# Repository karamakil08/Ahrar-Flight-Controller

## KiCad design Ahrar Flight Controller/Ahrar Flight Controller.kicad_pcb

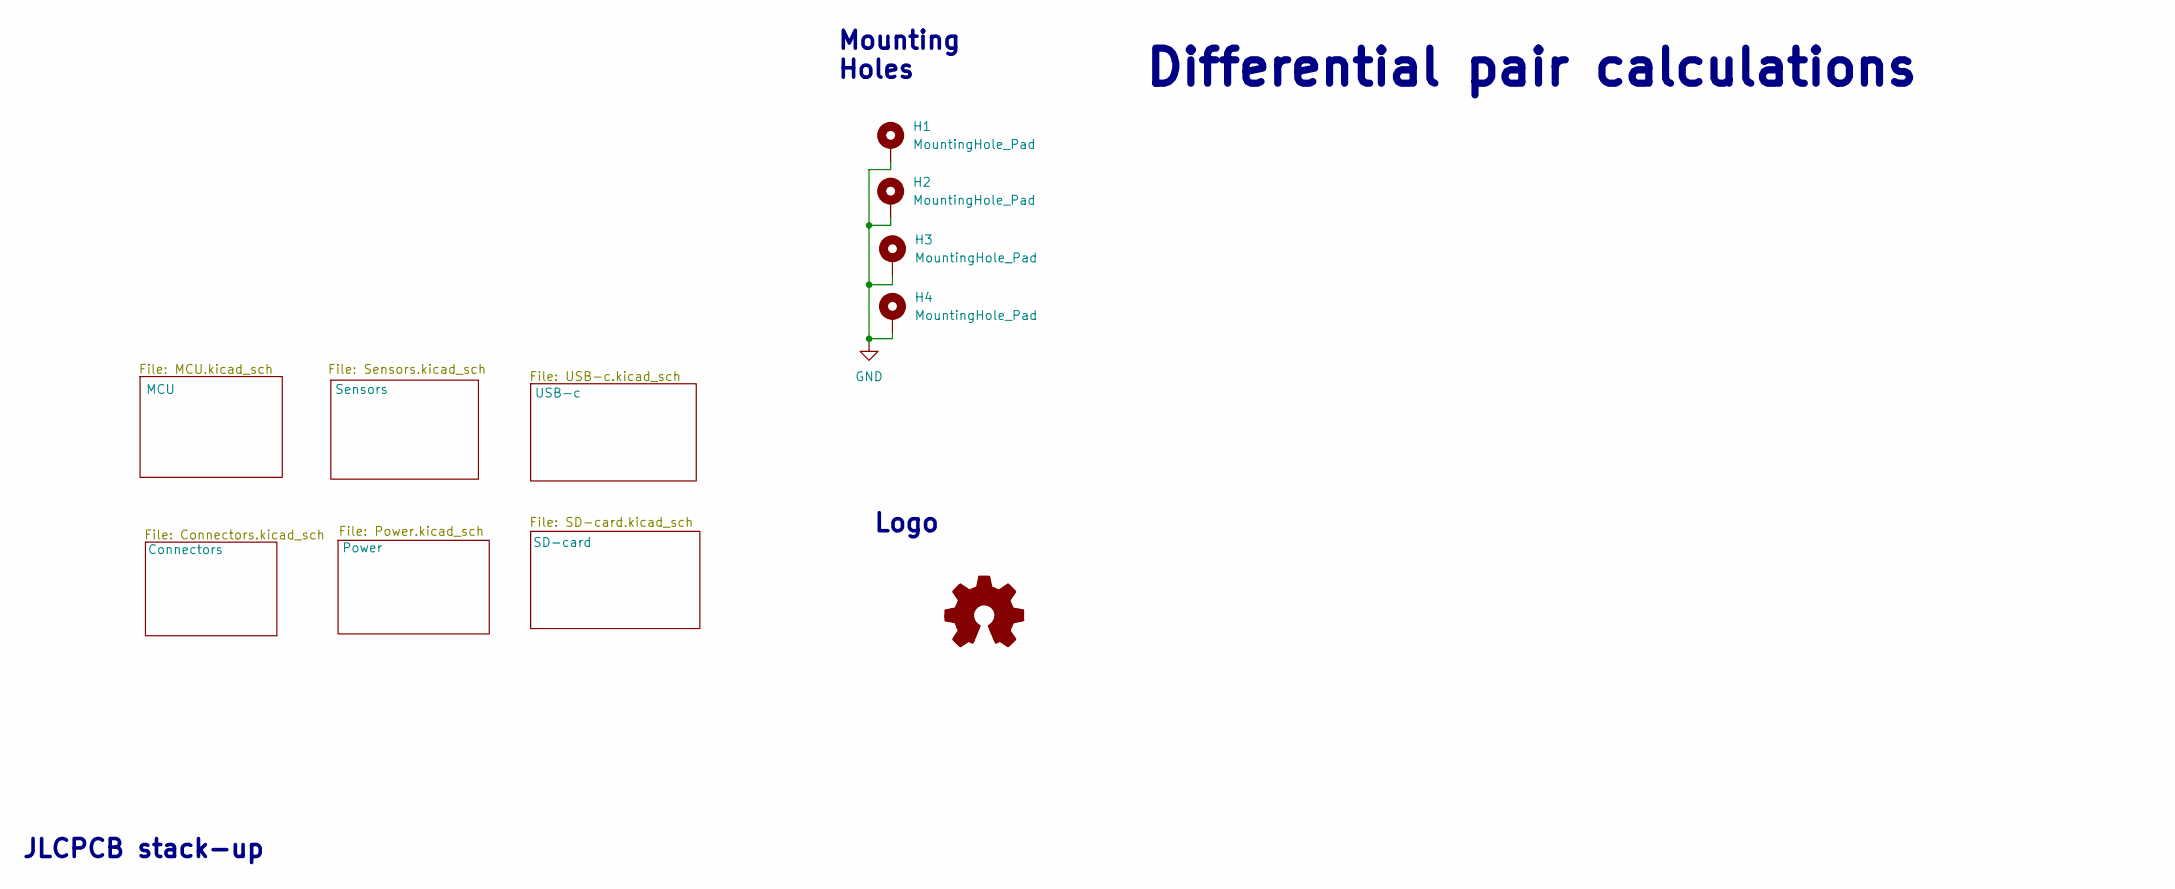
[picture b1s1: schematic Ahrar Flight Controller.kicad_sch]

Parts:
H1, H2, H3, H4: MountingHole_Pad; MountingHole_2.2mm_M2_Pad_Via
Logo1: Hananou logo

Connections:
GND: H1.1 (1_1), H2.1 (1_1), H3.1 (1_1), H4.1 (1_1); also elsewhere on the board

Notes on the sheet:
Differential pair calculations
Mounting Holes
JLCPCB stack-up
Logo

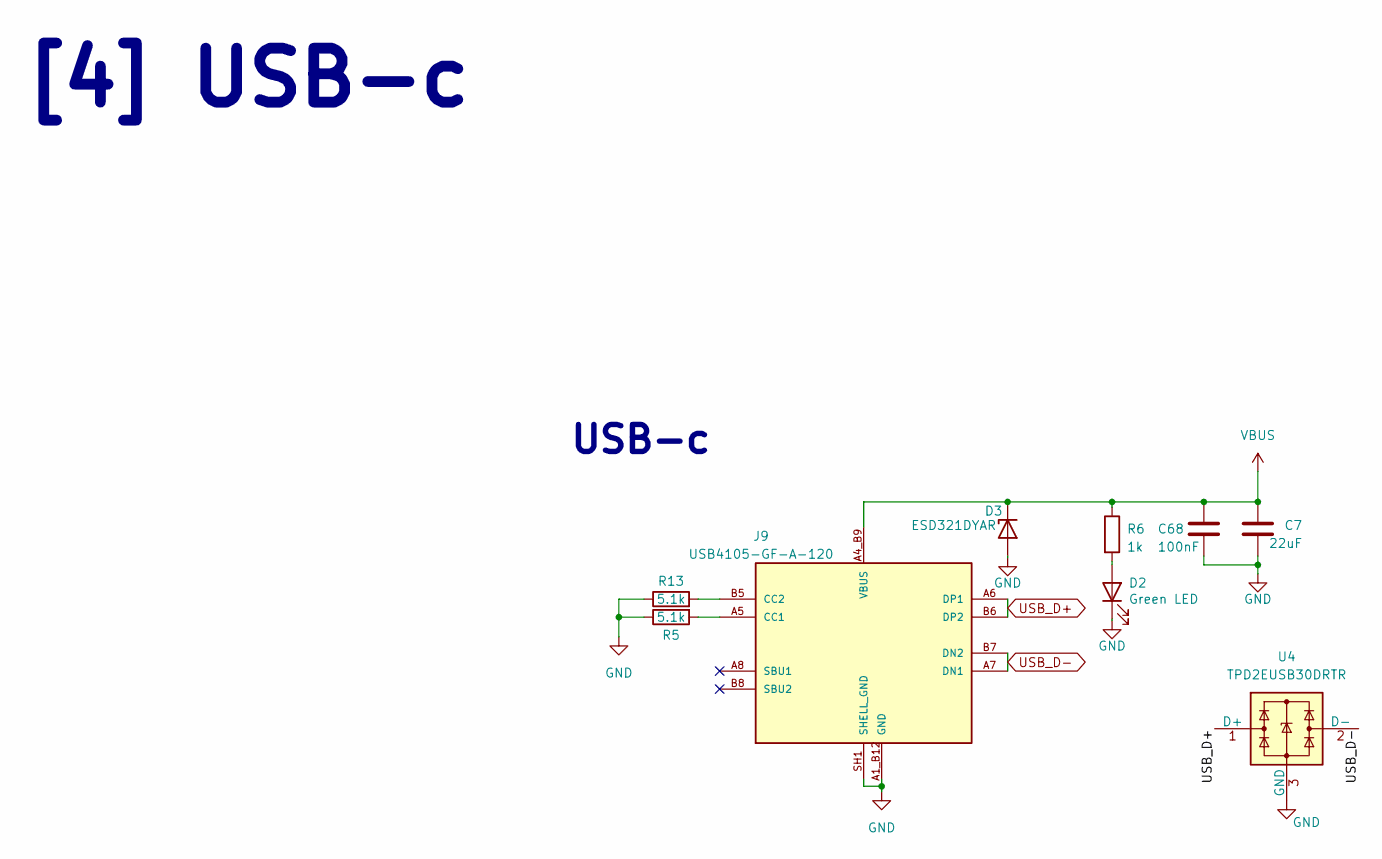
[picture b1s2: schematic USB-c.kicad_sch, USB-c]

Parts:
C7: 22uF; C_0805_2012Metric; Part Number CL21A226KOQNNNE
C68: 100nF; C_0402_1005Metric; Part Number GRM155R71C104KA88D
D2: Green LED; LED_0603_1608Metric; Part Number HL-PST-1608U51GC
D3: ESD321DYAR; D_SOD-523; Part Number ESD321DYAR
J9: USB4105-GF-A-120; GCT_USB4105-GF-A-120; Part Number USB4105-GF-A-120
R5, R13: 5.1k; R_0402_1005Metric; Part Number ERJ2RKF5101X
R6: 1k; R_0402_1005Metric; Part Number 0402WGJ0102TCE
U4: TPD2EUSB30DRTR; Texas_DRT-3

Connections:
GND: C7.2, C68.2, D2.1 (K), D3.2 (A), J9.A1_B12 (GND), J9.B1_A12 (GND), J9.SH1 (SHELL_GND), J9.SH2 (SHELL_GND), J9.SH3 (SHELL_GND), J9.SH4 (SHELL_GND), R5.1, R13.1, U4.3 (GND); also elsewhere on the board
unnamed: D2.2 (A), R6.2
unnamed: J9.A5 (CC1), R5.2
unnamed: J9.B5 (CC2), R13.2
USB_D+: J9.A6 (DP1), J9.B6 (DP2), U4.1 (D+); also elsewhere on the board
USB_D-: J9.A7 (DN1), J9.B7 (DN2), U4.2 (D-); also elsewhere on the board
VBUS: C7.1, C68.1, D3.1 (K), J9.A4_B9 (VBUS), J9.B4_A9 (VBUS), R6.1

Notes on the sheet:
USB-c
[4] USB-c

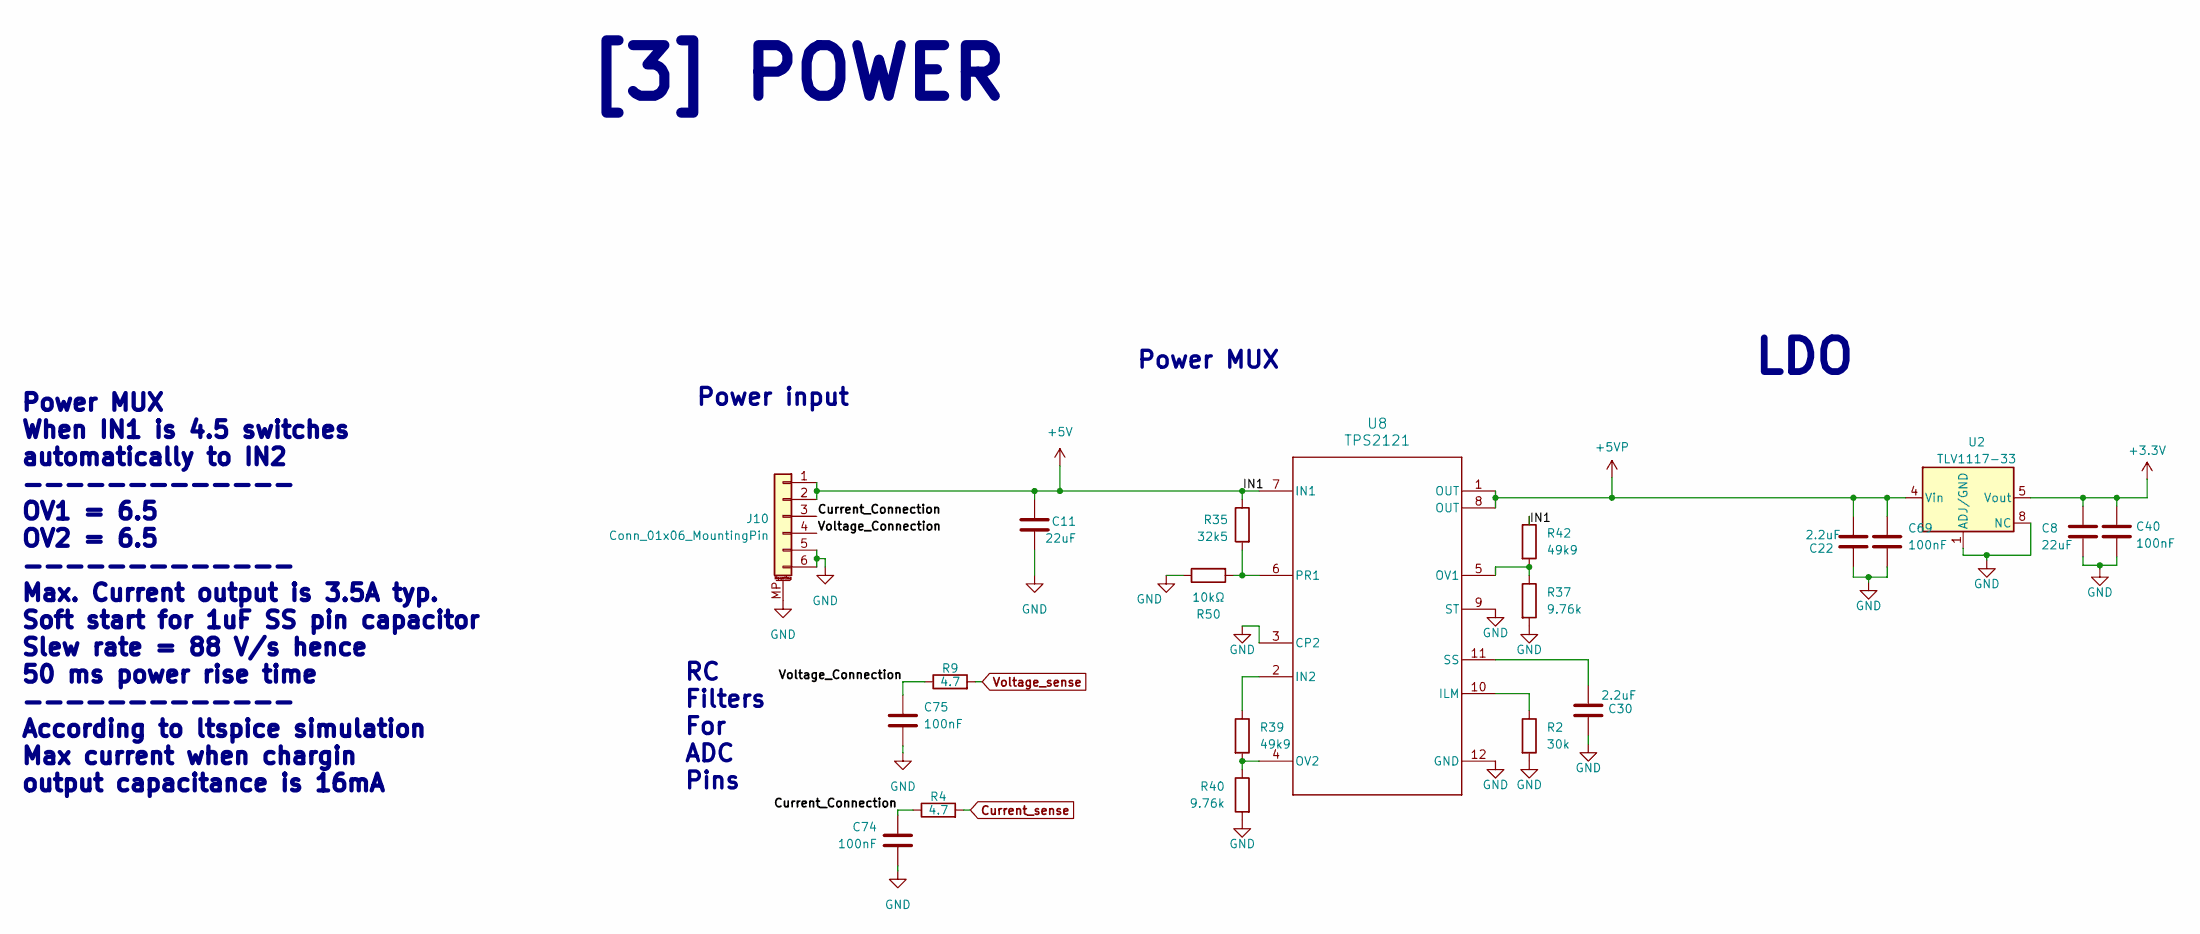
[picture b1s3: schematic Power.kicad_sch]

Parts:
C8, C11: 22uF; C_0805_2012Metric; Part Number CL21A226KOQNNNE
C22, C30: 2.2uF; C_0603_1608Metric; Part Number CL10B225KP8NNNC
C40, C69, C74, C75: 100nF; C_0402_1005Metric; Part Number GRM155R71C104KA88D
J10: Conn_01x06_MountingPin; Molex_CLIK-Mate_502494-0670_1x06-1MP_P2.00mm_Horizontal; Part Number 502494-0670
R2: 30k; R_0402_1005Metric; Part Number ERJ2RKF3002X
R4, R9: 4.7; R_0402_1005Metric; Part Number CQ02WGJ047JTCE
R35: 32k5; R_0402_1005Metric; Part Number 0402WGF3242TCE
R37, R40: 9.76k; R_0402_1005Metric; Part Number 0402WGF9761TCE
R39, R42: 49k9; R_0402_1005Metric; Part Number ERJ2RKF4992X
R50: 10kΩ; R_0402_1005Metric; Part Number ERJ2RKF1002X
U2: TLV1117-33; WSON-8-1EP_4x4mm_P0.8mm_EP2.2x3mm; Part Number TLV1117-33IDRJR
U8: TPS2121; RUX0012A; Part Number TPS2121RUXR

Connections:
+3.3V: C8.1, C40.1, U2.5 (Vout), U2.6 (Vout), U2.7 (Vout); also elsewhere on the board
+5V: C11.1, J10.1, J10.2, R35.1, R42.1, U8.7 (IN1); also elsewhere on the board
+5VP: C22.1, C69.1, U2.2 (Vin), U2.3 (Vin), U2.4 (Vin), U8.1 (OUT), U8.8 (OUT); also elsewhere on the board
/Power/Current_Connection: C74.1, J10.3, R4.1
/Power/Voltage_Connection: C75.1, J10.4, R9.1
Current_sense: R4.2; also elsewhere on the board
GND: C8.2, C11.2, C22.2, C30.2, C40.2, C69.2, C74.2, C75.2, J10.5, J10.6, J10.MP (MountPin), R2.2, R37.2, R40.2, R50.1, U2.1 (ADJ/GND), U2.8 (NC), U2.9 (PAD), U8.3 (CP2), U8.9 (ST), U8.12 (GND); also elsewhere on the board
unnamed: R2.1, U8.10 (ILM)
unnamed: R39.1, U8.2 (IN2)
unnamed: R37.1, R42.2, U8.5 (OV1)
unnamed: R39.2, R40.1, U8.4 (OV2)
unnamed: R35.2, R50.2, U8.6 (PR1)
unnamed: C30.1, U8.11 (SS)
Voltage_sense: R9.2; also elsewhere on the board

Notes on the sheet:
Power MUX
LDO
RC Filters For ADC Pins
[3] POWER
Power MUX When IN1 is 4.5 switches automatically to IN2 ------------- OV1 = 6.5 OV2 = 6.5 ------------- Max. Current output is 3.5A typ. Soft start for 1uF SS pin capacitor Slew rate = 88 V/s hence 50 ms power rise time ------------- According to ltspice simulation Max current when chargin output c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
Power input

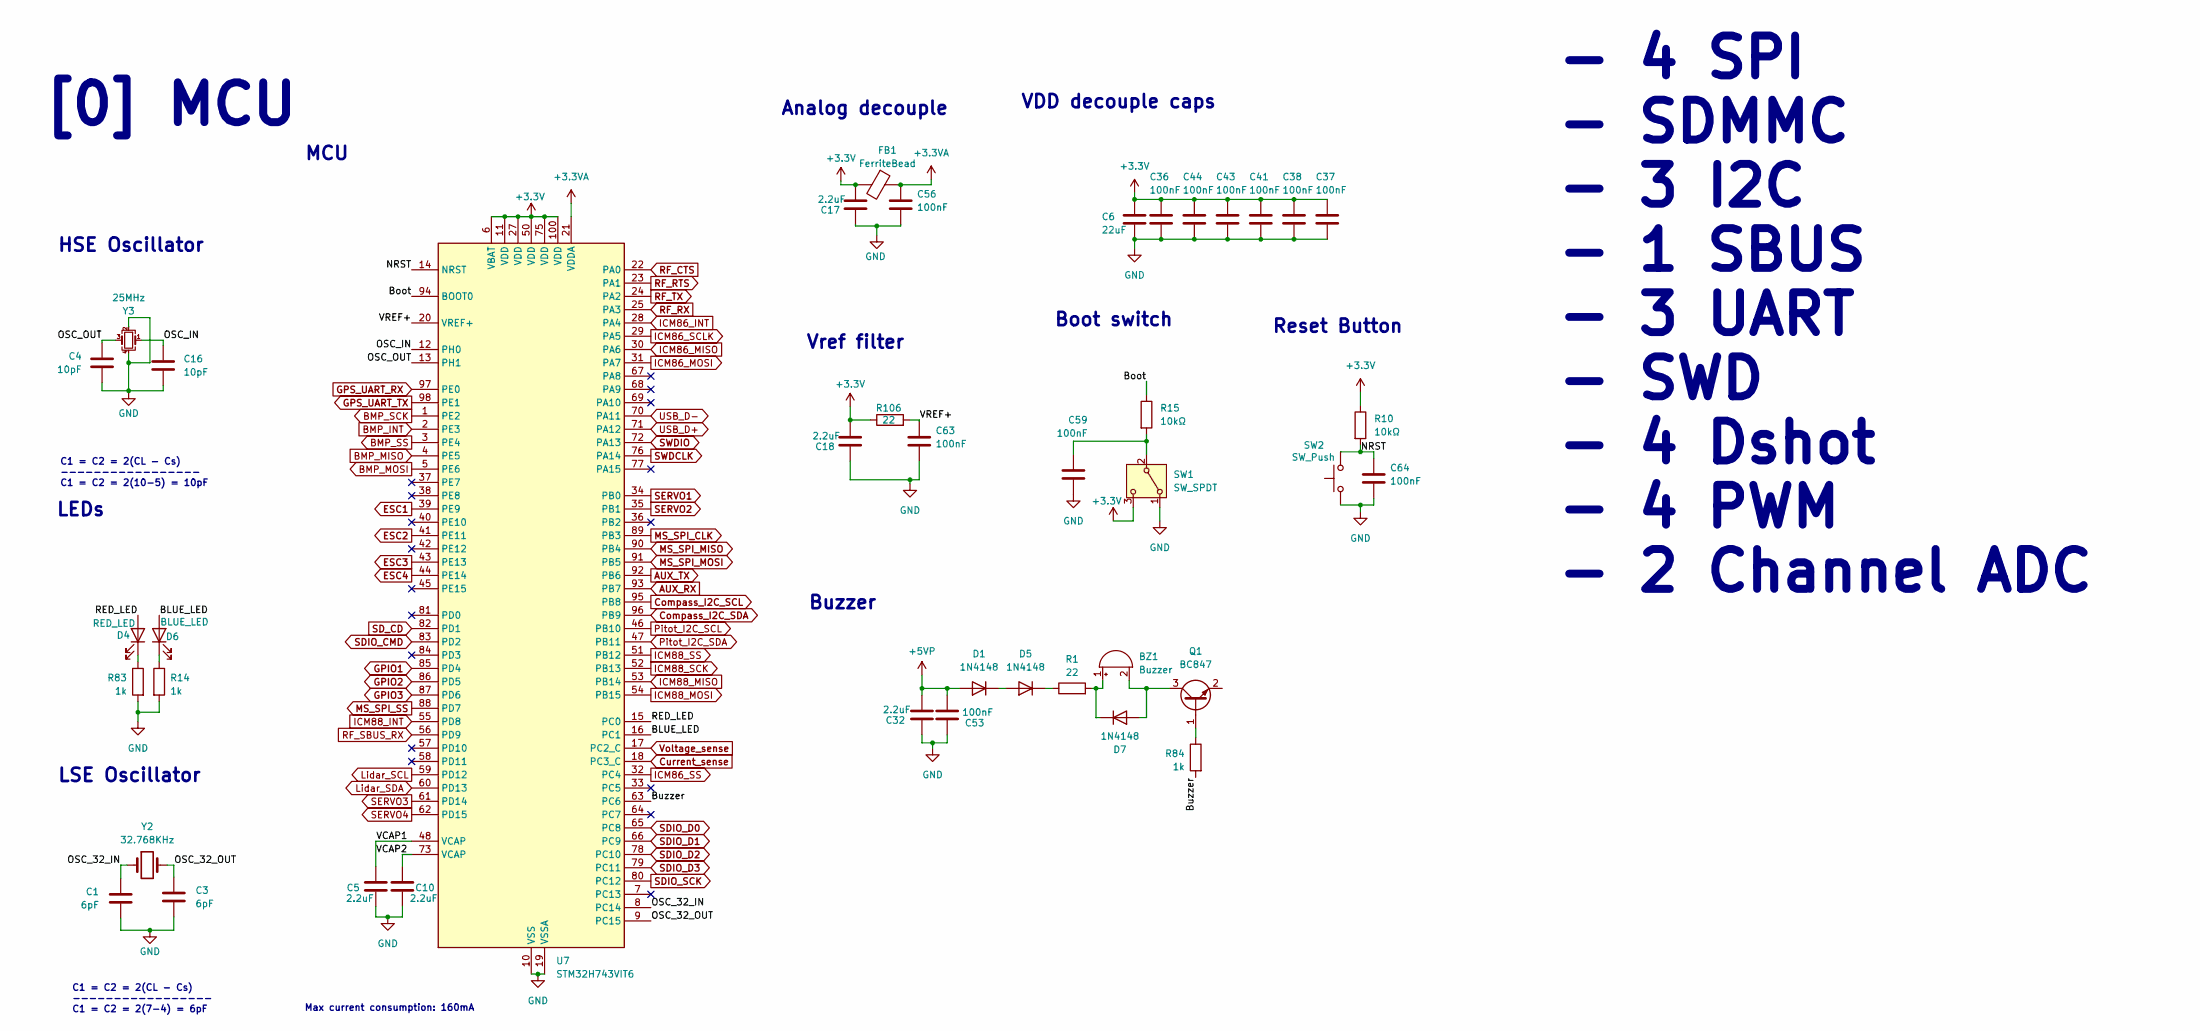
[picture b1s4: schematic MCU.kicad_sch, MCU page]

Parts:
BZ1: Buzzer; Buzzer_typeshit; Part Number L-KLS3-SMT-3020-3V
C1, C3: 6pF; C_0402_1005Metric; Part Number CC0402DRNPO9BN6R0
C4, C16: 10pF; C_0603_1608Metric; Part Number CL10C100JB81PNC
C5, C10, C17, C18, C32: 2.2uF; C_0603_1608Metric; Part Number CL10B225KP8NNNC
C6: 22uF; C_0805_2012Metric; Part Number CL21A226KOQNNNE
C36, C37, C38, C41, C43, C44, C53, C56, C59, C63, C64: 100nF; C_0402_1005Metric; Part Number GRM155R71C104KA88D
D1, D5, D7: 1N4148; D_SOD-523; Part Number 1N4148WT
D4: RED_LED; LED_0603_1608Metric; Part Number 27-21/R6C-AP1Q2B/3C
D6: BLUE_LED; LED_0603_1608Metric; Part Number HL-PST-1608H203BC
FB1: FerriteBead; R_0603_1608Metric; Part Number BLM18HE601SN1D
Q1: BC847; SOT-23
R1: 22; R_0603_1608Metric; Part Number ERJPA3J220V
R10, R15: 10kΩ; R_0402_1005Metric; Part Number ERJ2RKF1002X
R14, R83, R84: 1k; R_0402_1005Metric; Part Number 0402WGJ0102TCE
R106: 22; R_0402_1005Metric; Part Number CQ02WGF220JTCE
SW1: SW_SPDT; SW_SPDT_CK_JS102011SAQN; Part Number L-KLS7-MSK-12C03
SW2: SW_Push; SW_SPST_PTS810; Part Number PTS810 SJM 250 SMTR LFS
U7: STM32H743VIT6; LQFP-100_14x14mm_P0.5mm; Part Number STM32H743VIT6
Y2: 32.768KHz; Crystal_SMD_2012-2Pin_2.0x1.2mm; Part Number RT2012-32.768-7-TR
Y3: 25MHz; Oscillator_SMD_Abracon_ASDMB-4Pin_2.5x2.0mm; Part Number ECS-250-10-36Q-ES-TR

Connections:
+3.3V: C6.1, C17.1, C18.1, C36.1, C37.1, C38.1, C41.1, C43.1, C44.1, FB1.2, R10.1, R106.1, SW1.3 (C), U7.6 (VBAT), U7.11 (VDD), U7.27 (VDD), U7.50 (VDD), U7.75 (VDD), U7.100 (VDD); also elsewhere on the board
+3.3VA: C56.1, FB1.1, U7.21 (VDDA)
+5VP: C32.1, C53.1, D1.2 (A); also elsewhere on the board
/MCU/BLUE_LED: D6.2 (A), U7.16 (PC1)
/MCU/Boot: R15.1, U7.94 (BOOT0)
/MCU/Buzzer: R84.2, U7.63 (PC6)
/MCU/NRST: C64.1, R10.2, SW2.2, U7.14 (NRST)
/MCU/OSC_32_IN: C1.1, U7.8 (PC14), Y2.1
/MCU/OSC_32_OUT: C3.1, U7.9 (PC15), Y2.2
/MCU/OSC_IN: C16.1, U7.12 (PH0), Y3.1
/MCU/OSC_OUT: C4.1, U7.13 (PH1), Y3.3
/MCU/RED_LED: D4.2 (A), U7.15 (PC0)
/MCU/VCAP1: C5.2, U7.48 (VCAP)
/MCU/VCAP2: C10.2, U7.73 (VCAP)
/MCU/VREF+: C63.1, R106.2, U7.20 (VREF+)
AUX_RX: U7.93 (PB7); also elsewhere on the board
AUX_TX: U7.92 (PB6); also elsewhere on the board
BMP_INT: U7.2 (PE3); also elsewhere on the board
BMP_MISO: U7.4 (PE5); also elsewhere on the board
BMP_MOSI: U7.5 (PE6); also elsewhere on the board
BMP_SCK: U7.1 (PE2); also elsewhere on the board
BMP_SS: U7.3 (PE4); also elsewhere on the board
Compass_I2C_SCL: U7.95 (PB8); also elsewhere on the board
Compass_I2C_SDA: U7.96 (PB9); also elsewhere on the board
Current_sense: U7.18 (PC3_C); also elsewhere on the board
ESC1: U7.39 (PE9); also elsewhere on the board
ESC2: U7.41 (PE11); also elsewhere on the board
ESC3: U7.43 (PE13); also elsewhere on the board
ESC4: U7.44 (PE14); also elsewhere on the board
GND: C1.2, C3.2, C4.2, C5.1, C6.2, C10.1, C16.2, C17.2, C18.2, C32.2, C36.2, C37.2, C38.2, C41.2, C43.2, C44.2, C53.2, C56.2, C59.2, C63.2, C64.2, R14.2, R83.2, SW1.1 (A), SW2.1, U7.10 (VSS), U7.19 (VSSA), U7.26 (VSS), U7.49 (VSS), U7.74 (VSS), U7.99 (VSS), Y3.2, Y3.4; also elsewhere on the board
GPIO1: U7.85 (PD4); also elsewhere on the board
GPIO2: U7.86 (PD5); also elsewhere on the board
GPIO3: U7.87 (PD6); also elsewhere on the board
GPS_UART_RX: U7.97 (PE0); also elsewhere on the board
GPS_UART_TX: U7.98 (PE1); also elsewhere on the board
ICM86_INT: U7.28 (PA4); also elsewhere on the board
ICM86_MISO: U7.30 (PA6); also elsewhere on the board
ICM86_MOSI: U7.31 (PA7); also elsewhere on the board
ICM86_SCLK: U7.29 (PA5); also elsewhere on the board
ICM86_SS: U7.32 (PC4); also elsewhere on the board
ICM88_INT: U7.55 (PD8); also elsewhere on the board
ICM88_MISO: U7.53 (PB14); also elsewhere on the board
ICM88_MOSI: U7.54 (PB15); also elsewhere on the board
ICM88_SCK: U7.52 (PB13); also elsewhere on the board
ICM88_SS: U7.51 (PB12); also elsewhere on the board
Lidar_SCL: U7.59 (PD12); also elsewhere on the board
Lidar_SDA: U7.60 (PD13); also elsewhere on the board
MS_SPI_CLK: U7.89 (PB3); also elsewhere on the board
MS_SPI_MISO: U7.90 (PB4); also elsewhere on the board
MS_SPI_MOSI: U7.91 (PB5); also elsewhere on the board
MS_SPI_SS: U7.88 (PD7); also elsewhere on the board
unnamed: BZ1.1 (+), D7.1 (K), R1.2
unnamed: BZ1.2 (-), D7.2 (A), Q1.3 (C)
unnamed: D1.1 (K), D5.2 (A)
unnamed: D4.1 (K), R83.1
unnamed: D5.1 (K), R1.1
unnamed: D6.1 (K), R14.1
unnamed: Q1.1 (B), R84.1
unnamed: C59.1, R15.2, SW1.2 (B)
Pitot_I2C_SCL: U7.46 (PB10); also elsewhere on the board
Pitot_I2C_SDA: U7.47 (PB11); also elsewhere on the board
RF_CTS: U7.22 (PA0); also elsewhere on the board
RF_RTS: U7.23 (PA1); also elsewhere on the board
RF_RX: U7.25 (PA3); also elsewhere on the board
RF_SBUS_RX: U7.56 (PD9); also elsewhere on the board
RF_TX: U7.24 (PA2); also elsewhere on the board
SDIO_CMD: U7.83 (PD2); also elsewhere on the board
SDIO_D0: U7.65 (PC8); also elsewhere on the board
SDIO_D1: U7.66 (PC9); also elsewhere on the board
SDIO_D2: U7.78 (PC10); also elsewhere on the board
SDIO_D3: U7.79 (PC11); also elsewhere on the board
SDIO_SCK: U7.80 (PC12); also elsewhere on the board
SD_CD: U7.82 (PD1); also elsewhere on the board
SERVO1: U7.34 (PB0); also elsewhere on the board
SERVO2: U7.35 (PB1); also elsewhere on the board
SERVO3: U7.61 (PD14); also elsewhere on the board
SERVO4: U7.62 (PD15); also elsewhere on the board
SWDCLK: U7.76 (PA14); also elsewhere on the board
SWDIO: U7.72 (PA13); also elsewhere on the board
USB_D+: U7.71 (PA12); also elsewhere on the board
USB_D-: U7.70 (PA11); also elsewhere on the board
Voltage_sense: U7.17 (PC2_C); also elsewhere on the board

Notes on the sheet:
C1 = C2 = 2(CL - Cs) ----------------- C1 = C2 = 2(7-4) = 6pF
Max current consumption: 160mA
MCU
C1 = C2 = 2(CL - Cs) ----------------- C1 = C2 = 2(10-5) = 10pF
VDD decouple caps
LEDs
Reset Button
Vref filter
- 4 SPI - SDMMC - 3 I2C - 1 SBUS - 3 UART - SWD - 4 Dshot - 4 PWM - 2 Channel ADC
Boot switch
LSE Oscillator
Analog decouple
Buzzer
HSE Oscillator
[0] MCU

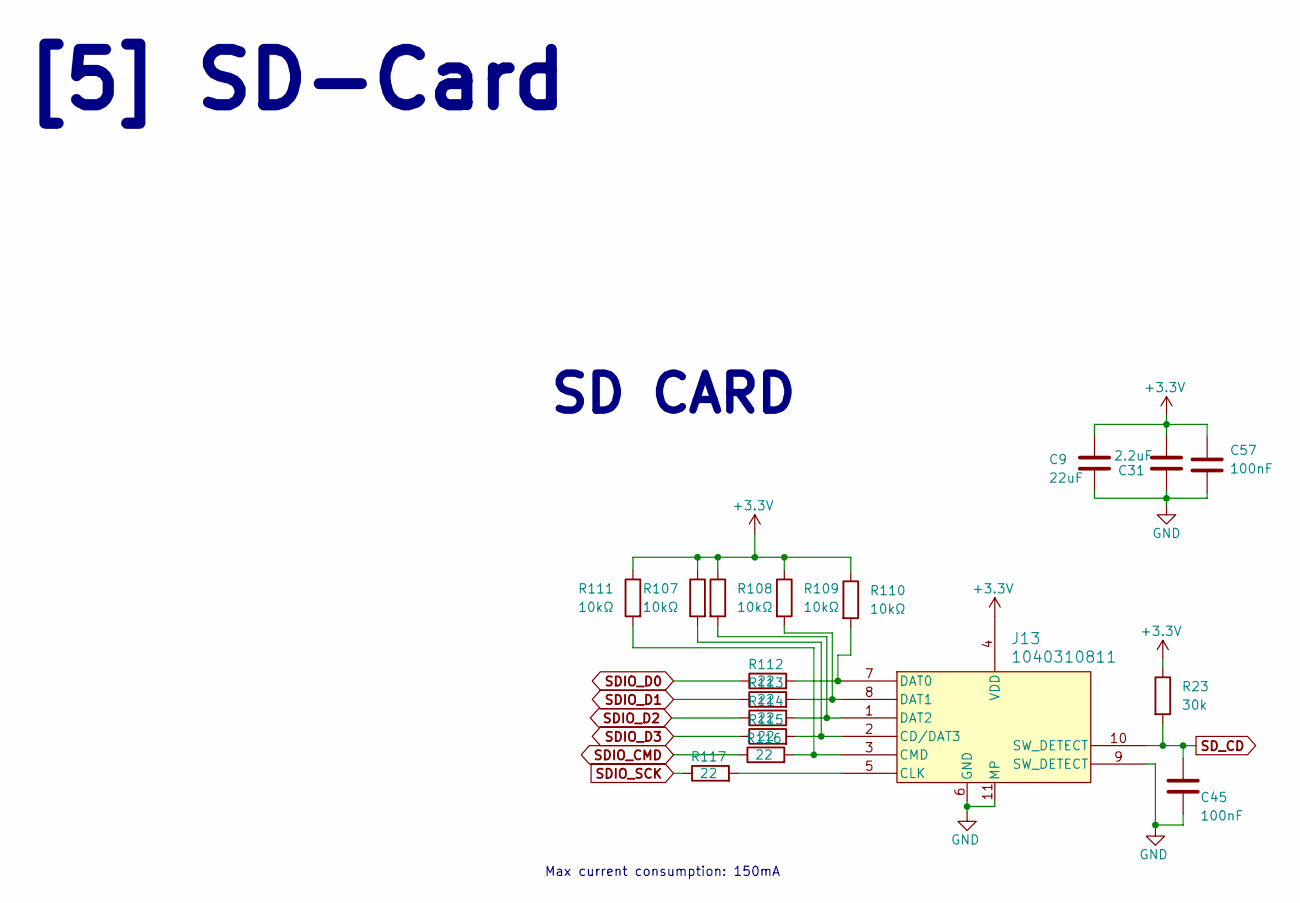
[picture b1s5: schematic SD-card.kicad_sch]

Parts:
C9: 22uF; C_0805_2012Metric; Part Number CL21A226KOQNNNE
C31: 2.2uF; C_0603_1608Metric; Part Number CL10B225KP8NNNC
C45, C57: 100nF; C_0402_1005Metric; Part Number GRM155R71C104KA88D
J13: 1040310811; 104031-0811_MOL; Part Number 104031-0811
R23: 30k; R_0402_1005Metric; Part Number ERJ2RKF3002X
R107, R108, R109, R110, R111: 10kΩ; R_0402_1005Metric; Part Number ERJ2RKF1002X
R112, R113, R114, R115, R116, R117: 22; R_0402_1005Metric; Part Number CQ02WGF220JTCE

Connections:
+3.3V: C9.1, C31.1, C57.1, J13.4 (VDD), R23.1, R107.1, R108.1, R109.1, R110.1, R111.1; also elsewhere on the board
GND: C9.2, C31.2, C45.2, C57.2, J13.6 (GND), J13.9 (SW_DETECT), J13.11 (MP), J13.12 (MP), J13.13 (MP), J13.14 (MP); also elsewhere on the board
unnamed: J13.2 (CD/DAT3), R107.2, R115.2
unnamed: J13.5 (CLK), R117.2
unnamed: J13.3 (CMD), R111.2, R116.2
unnamed: J13.7 (DAT0), R110.2, R112.2
unnamed: J13.8 (DAT1), R109.2, R113.2
unnamed: J13.1 (DAT2), R108.2, R114.2
SDIO_CMD: R116.1; also elsewhere on the board
SDIO_D0: R112.1; also elsewhere on the board
SDIO_D1: R113.1; also elsewhere on the board
SDIO_D2: R114.1; also elsewhere on the board
SDIO_D3: R115.1; also elsewhere on the board
SDIO_SCK: R117.1; also elsewhere on the board
SD_CD: C45.1, J13.10 (SW_DETECT), R23.2; also elsewhere on the board

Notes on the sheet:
[5] SD-Card
Max current consumption: 150mA
SD CARD

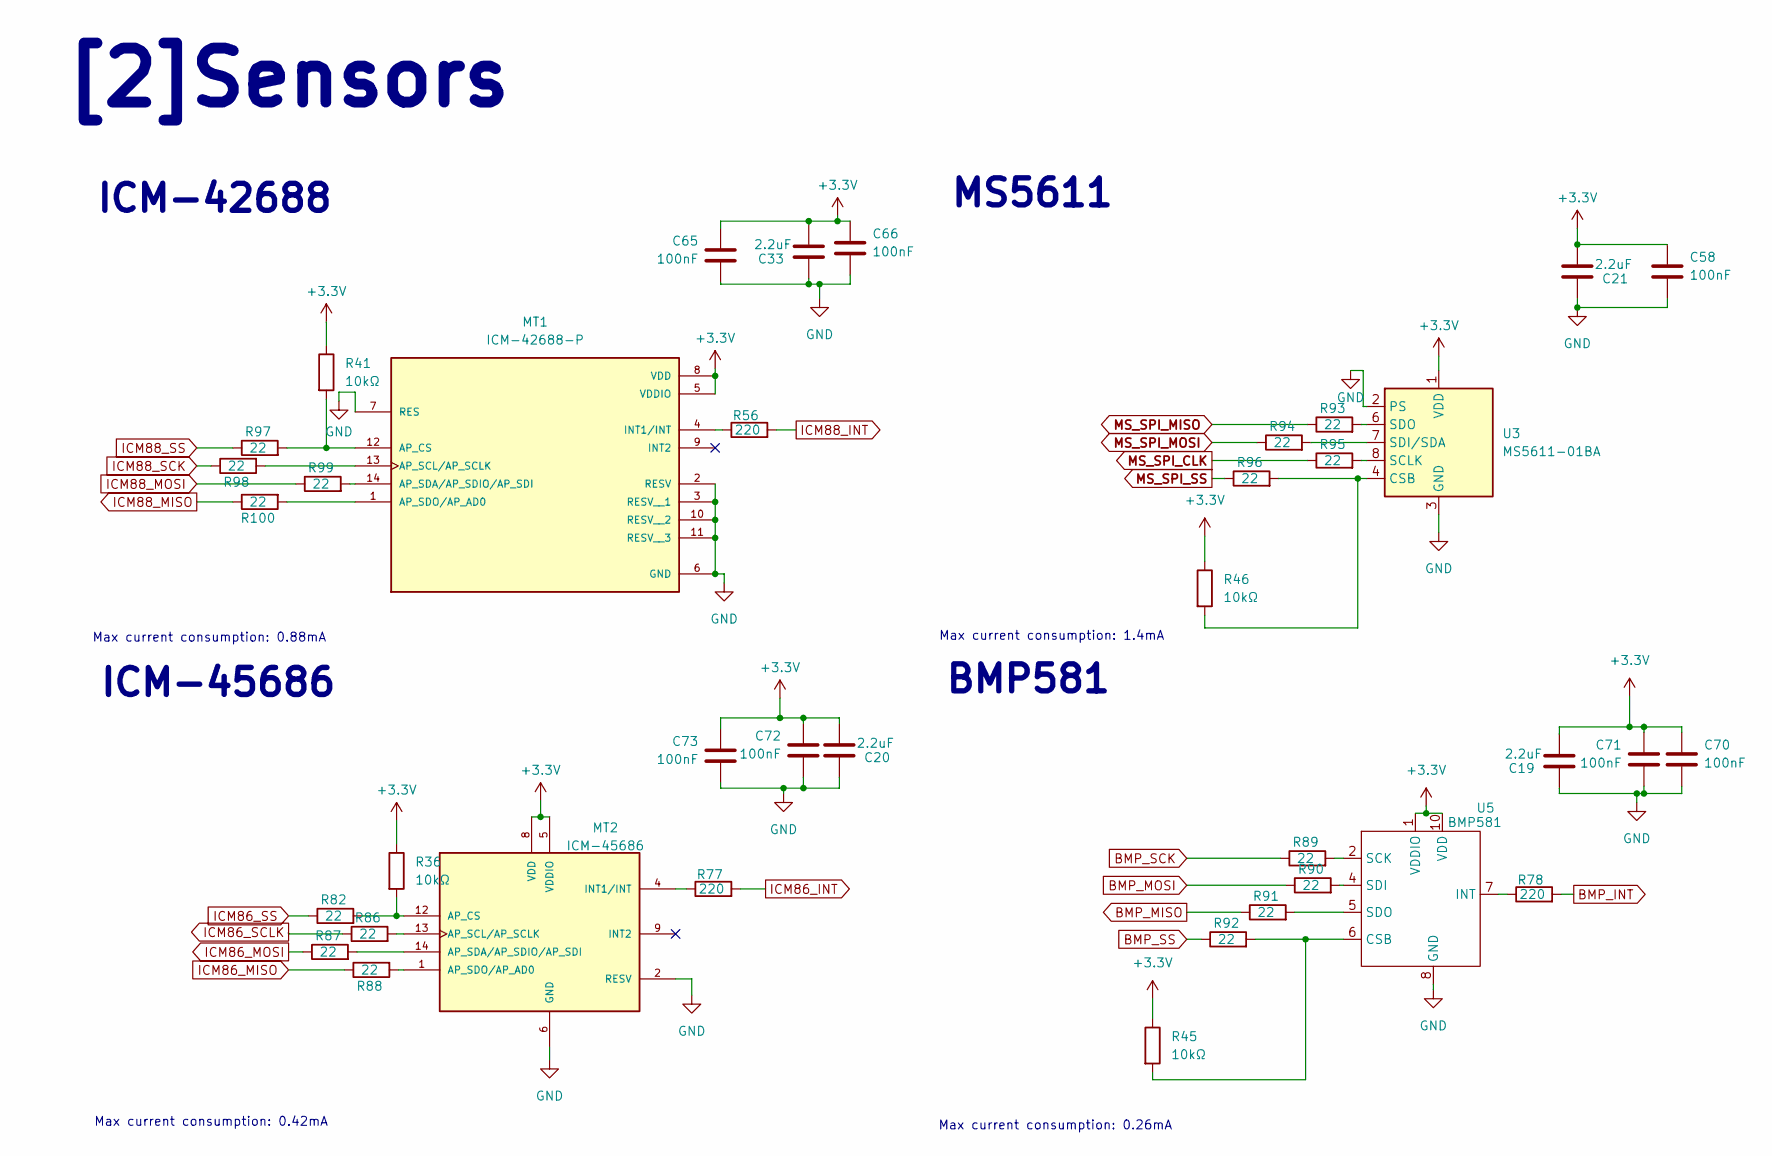
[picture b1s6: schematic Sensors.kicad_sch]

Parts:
C19, C20, C21, C33: 2.2uF; C_0603_1608Metric; Part Number CL10B225KP8NNNC
C58, C65, C66, C70, C71, C72, C73: 100nF; C_0402_1005Metric; Part Number GRM155R71C104KA88D
MT1: ICM-42688-P; LGA14_2P5X3X0P91_TDK-L; PARTREV 1.1
MT2: ICM-45686; LGA14_2P5X3X0P91_TDK-L; PARTREV 1.1
R36, R41, R45, R46: 10kΩ; R_0402_1005Metric; Part Number ERJ2RKF1002X
R56, R77, R78: 220; R_0402_1005Metric; Part Number ERJ2RKF2200X
R82, R86, R87, R88, R89, R90, R91, R92, R93, R94, R95, R96, R97, R98, R99, R100: 22; R_0402_1005Metric; Part Number CQ02WGF220JTCE
U3: MS5611-01BA; LGA-8_3x5mm_P1.25mm
U5: BMP581; Part Number BMP581

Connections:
+3.3V: C19.1, C20.1, C21.1, C33.1, C58.1, C65.1, C66.1, C70.1, C71.1, C72.1, C73.1, MT1.5 (VDDIO), MT1.8 (VDD), MT2.5 (VDDIO), MT2.8 (VDD), R36.1, R41.1, R45.1, R46.1, U3.1 (VDD), U5.1 (VDDIO), U5.10 (VDD); also elsewhere on the board
BMP_INT: R78.2; also elsewhere on the board
BMP_MISO: R91.1; also elsewhere on the board
BMP_MOSI: R90.1; also elsewhere on the board
BMP_SCK: R89.1; also elsewhere on the board
BMP_SS: R92.1; also elsewhere on the board
GND: C19.2, C20.2, C21.2, C33.2, C58.2, C65.2, C66.2, C70.2, C71.2, C72.2, C73.2, MT1.2 (RESV), MT1.3 (RESV__1), MT1.6 (GND), MT1.7 (RES), MT1.10 (RESV__2), MT1.11 (RESV__3), MT2.2 (RESV), MT2.3 (RESV__1), MT2.6 (GND), MT2.7 (RESV), MT2.10 (RESV__2), MT2.11 (RESV__3), U3.2 (PS), U3.3 (GND), U5.3 (GND), U5.8 (GND), U5.9 (GND); also elsewhere on the board
ICM86_INT: R77.2; also elsewhere on the board
ICM86_MISO: R88.1; also elsewhere on the board
ICM86_MOSI: R87.1; also elsewhere on the board
ICM86_SCLK: R86.1; also elsewhere on the board
ICM86_SS: R82.1; also elsewhere on the board
ICM88_INT: R56.2; also elsewhere on the board
ICM88_MISO: R100.1; also elsewhere on the board
ICM88_MOSI: R99.1; also elsewhere on the board
ICM88_SCK: R98.1; also elsewhere on the board
ICM88_SS: R97.1; also elsewhere on the board
MS_SPI_CLK: R95.1; also elsewhere on the board
MS_SPI_MISO: R93.1; also elsewhere on the board
MS_SPI_MOSI: R94.1; also elsewhere on the board
MS_SPI_SS: R96.1; also elsewhere on the board
unnamed: MT1.12 (AP_CS), R41.2, R97.2
unnamed: MT1.13 (AP_SCL/AP_SCLK), R98.2
unnamed: MT1.14 (AP_SDA/AP_SDIO/AP_SDI), R99.2
unnamed: MT1.1 (AP_SDO/AP_AD0), R100.2
unnamed: MT1.4 (INT1/INT), R56.1
unnamed: MT2.12 (AP_CS), R36.2, R82.2
unnamed: MT2.13 (AP_SCL/AP_SCLK), R86.2
unnamed: MT2.14 (AP_SDA/AP_SDIO/AP_SDI), R87.2
unnamed: MT2.1 (AP_SDO/AP_AD0), R88.2
unnamed: MT2.4 (INT1/INT), R77.1
unnamed: R46.2, R96.2, U3.4 (CSB), U3.5 (CSB)
unnamed: R95.2, U3.8 (SCLK)
unnamed: R94.2, U3.7 (SDI/SDA)
unnamed: R93.2, U3.6 (SDO)
unnamed: R45.2, R92.2, U5.6 (CSB)
unnamed: R78.1, U5.7 (INT)
unnamed: R89.2, U5.2 (SCK)
unnamed: R90.2, U5.4 (SDI)
unnamed: R91.2, U5.5 (SDO)

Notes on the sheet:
Max current consumption: 0.26mA
MS5611
BMP581
ICM-42688
Max current consumption: 1.4mA
Max current consumption: 0.42mA
ICM-45686
Max current consumption: 0.88mA
[2]Sensors

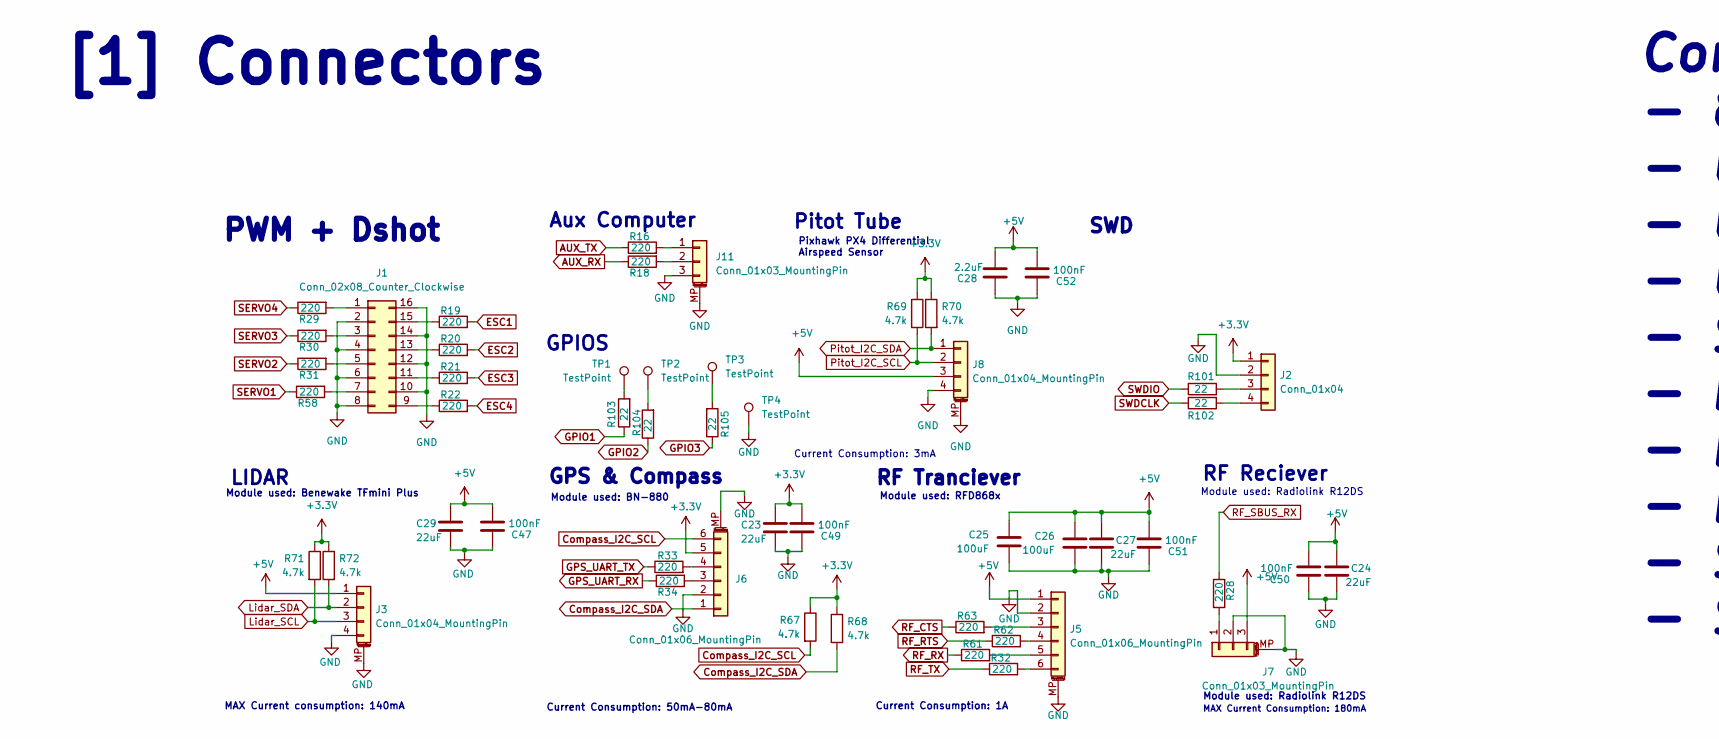
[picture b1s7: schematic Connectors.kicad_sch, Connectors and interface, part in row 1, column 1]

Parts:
C23, C24, C27, C29: 22uF; C_0805_2012Metric; Part Number CL21A226KOQNNNE
C25, C26: 100uF; CP_EIA-6032-20_AVX-F; Part Number 293D107X0010C2TE3
C28: 2.2uF; C_0603_1608Metric; Part Number CL10B225KP8NNNC
C47, C49, C50, C51, C52: 100nF; C_0402_1005Metric; Part Number GRM155R71C104KA88D
J1: Conn_02x08_Counter_Clockwise; PinHeader_2x08_P2.54mm_Horizontal; Part Number DS1022-2X8RF11-B
J2: Conn_01x04; PinHeader_1x04_P2.54mm_Vertical; Part Number 22-28-4046
J3, J8: Conn_01x04_MountingPin; JST_GH_SM04B-GHS-TB_1x04-1MP_P1.25mm_Horizontal; Part Number SM04B-GHS-TB(LF)(SN)
J5: Conn_01x06_MountingPin; Molex_CLIK-Mate_502494-0670_1x06-1MP_P2.00mm_Horizontal; Part Number 502494-0670
J6: Conn_01x06_MountingPin; JST_GH_SM06B-GHS-TB_1x06-1MP_P1.25mm_Horizontal; Part Number SM06B-GHS-TB
J7, J11: Conn_01x03_MountingPin; JST_GH_SM03B-GHS-TB_1x03-1MP_P1.25mm_Horizontal; Part Number SM03B-GHS-TB(LF)(SN)
R16, R18, R19, R20, R21, R22, R28, R29, R30, R31, R32, R33, R34, R58, R61, R62, R63: 220; R_0402_1005Metric; Part Number ERJ2RKF2200X
R67, R68, R69, R70, R71, R72: 4.7k; R_0402_1005Metric; Part Number ERJ2RKF4701X
R101, R102, R103, R104, R105: 22; R_0402_1005Metric; Part Number CQ02WGF220JTCE
TP1, TP2, TP3, TP4: TestPoint; TestPoint_Pad_1.0x1.0mm

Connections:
+3.3V: C23.1, C49.1, J2.1, J6.5, R67.1, R68.1, R69.1, R70.1, R71.1, R72.1; also elsewhere on the board
+5V: C24.1, C25.1, C26.1, C27.1, C28.1, C29.1, C47.1, C50.1, C51.1, C52.1, J3.1, J5.1, J7.3, J8.3; also elsewhere on the board
AUX_RX: R18.1; also elsewhere on the board
AUX_TX: R16.1; also elsewhere on the board
Compass_I2C_SCL: J6.6, R67.2; also elsewhere on the board
Compass_I2C_SDA: J6.1, R68.2; also elsewhere on the board
ESC1: R19.2; also elsewhere on the board
ESC2: R20.2; also elsewhere on the board
ESC3: R21.2; also elsewhere on the board
ESC4: R22.2; also elsewhere on the board
GND: C23.2, C24.2, C25.2, C26.2, C27.2, C28.2, C29.2, C47.2, C49.2, C50.2, C51.2, C52.2, J1.2, J1.4, J1.6, J1.8, J1.10, J1.12, J1.14, J1.16, J2.2, J3.4, J3.MP (MountPin), J5.2, J5.MP (MountPin), J6.2, J6.MP (MountPin), J7.2, J7.MP (MountPin), J8.4, J8.MP (MountPin), J11.3, J11.MP (MountPin), TP4.1 (1_1); also elsewhere on the board
GPIO1: R103.1; also elsewhere on the board
GPIO2: R104.1; also elsewhere on the board
GPIO3: R105.1; also elsewhere on the board
GPS_UART_RX: R34.1; also elsewhere on the board
GPS_UART_TX: R33.1; also elsewhere on the board
Lidar_SCL: J3.3, R71.2; also elsewhere on the board
Lidar_SDA: J3.2, R72.2; also elsewhere on the board
unnamed: J1.1, R29.2
unnamed: J1.3, R30.2
unnamed: J1.5, R31.2
unnamed: J1.7, R58.2
unnamed: J1.9, R22.1
unnamed: J1.11, R21.1
unnamed: J1.13, R20.1
unnamed: J1.15, R19.1
unnamed: J2.3, R101.2
unnamed: J2.4, R102.2
unnamed: J5.3, R63.2
unnamed: J5.4, R62.2
unnamed: J5.5, R61.2
unnamed: J5.6, R32.2
unnamed: J6.3, R34.2
unnamed: J6.4, R33.2
unnamed: J7.1, R28.2
unnamed: J11.1, R16.2
unnamed: J11.2, R18.2
unnamed: R103.2, TP1.1 (1_1)
unnamed: R104.2, TP2.1 (1_1)
unnamed: R105.2, TP3.1 (1_1)
Pitot_I2C_SCL: J8.2, R69.2; also elsewhere on the board
Pitot_I2C_SDA: J8.1, R70.2; also elsewhere on the board
RF_CTS: R63.1; also elsewhere on the board
RF_RTS: R62.1; also elsewhere on the board
RF_RX: R61.1; also elsewhere on the board
RF_SBUS_RX: R28.1; also elsewhere on the board
RF_TX: R32.1; also elsewhere on the board
SERVO1: R58.1; also elsewhere on the board
SERVO2: R31.1; also elsewhere on the board
SERVO3: R30.1; also elsewhere on the board
SERVO4: R29.1; also elsewhere on the board
SWDCLK: R102.1; also elsewhere on the board
SWDIO: R101.1; also elsewhere on the board

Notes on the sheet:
MAX Current consumption: 140mA
RF Reciever
Current Consumption: 50mA-80mA
Module used: Radiolink R12DS
LIDAR
Module used: BN-880
[1] Connectors
Current Consumption: 1A
Connections: - 8 PWM for ESCs and Servo motors - UART for GPS with a manetometer - UART for RF tranciever to communicate with GCS - UART for Auxiliary computer - SBUS (UART Reciever) for RF Reciever - I2C for pitot tube - I2C for Compass - I2C for Lidar - SWD - SDMCC for SD card
MAX Current Consumption: 180mA
Module used: Benewake TFmini Plus
Module used: RFD868x
SWD
RF Tranciever
Pixhawk PX4 Differential Airspeed Sensor
Current Consumption: 3mA
Pitot Tube
Aux Computer
GPS & Compass
GPIOS
PWM + Dshot
